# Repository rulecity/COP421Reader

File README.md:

# COP421Reader
This is a hardware reader for the COP421 Microcontroller.

I designed it very quickly just to read the COP421 microcontroller used by the RDI Halcyon (since I have/had one temporarily on loan).  It turns out it's identical to the Thayer's Quest arcade COP421 program, but it's nice to know for sure.

I relied heavily on the information at this page to contruct my reader: http://john.ccac.rwth-aachen.de:8000/patrick/COPSreader.htm

## Building
### KiCad files
I started with an EAGLE project that I made for Star Rider for this PCB, so you will see references to Star Rider in the Kicad project.  I imported some EAGLE symbols and used some native Kicad symbols so you'll see a hybrid of both.  (like I said, this was a quick n' dirty project since I intended it to only be used once).  I used KiCad v6 for this project.

### AVR files
Source code for the ATMega644p microcontroller, as well as a Makefile and a script to install via AVR Dragon / AVRDude.
The AVR reads from the COP421 and outputs the resulting data to USB serial port.

### Desktop
Source code to build a simple desktop (Windows/Linux/Mac) application to read the data from the AVR (via USB serial port) and save to a file.

### Bill of Materials
CSV file showing which parts I used on the PCB.

## Running
- Put COP421 into ZIF socket in custom PCB.
- Power on custom PCB with 5V wall wart.
- Plug in USB cable from desktop device (Windows/Linux/Mac) into custom PCB.  The USB serial device should be registered automatically.
- Run the desktop command line application.  You should see a "Listening" prompt.
- Hit the RESET button on the custom PCB.
- After a few seconds, the desktop app should report CRC success or fail.  On success, it will report the file path that it has written the dumped binary to.  You may repeat this (by repeatedly pressing RESET) to confirm that you've got a consistent read.

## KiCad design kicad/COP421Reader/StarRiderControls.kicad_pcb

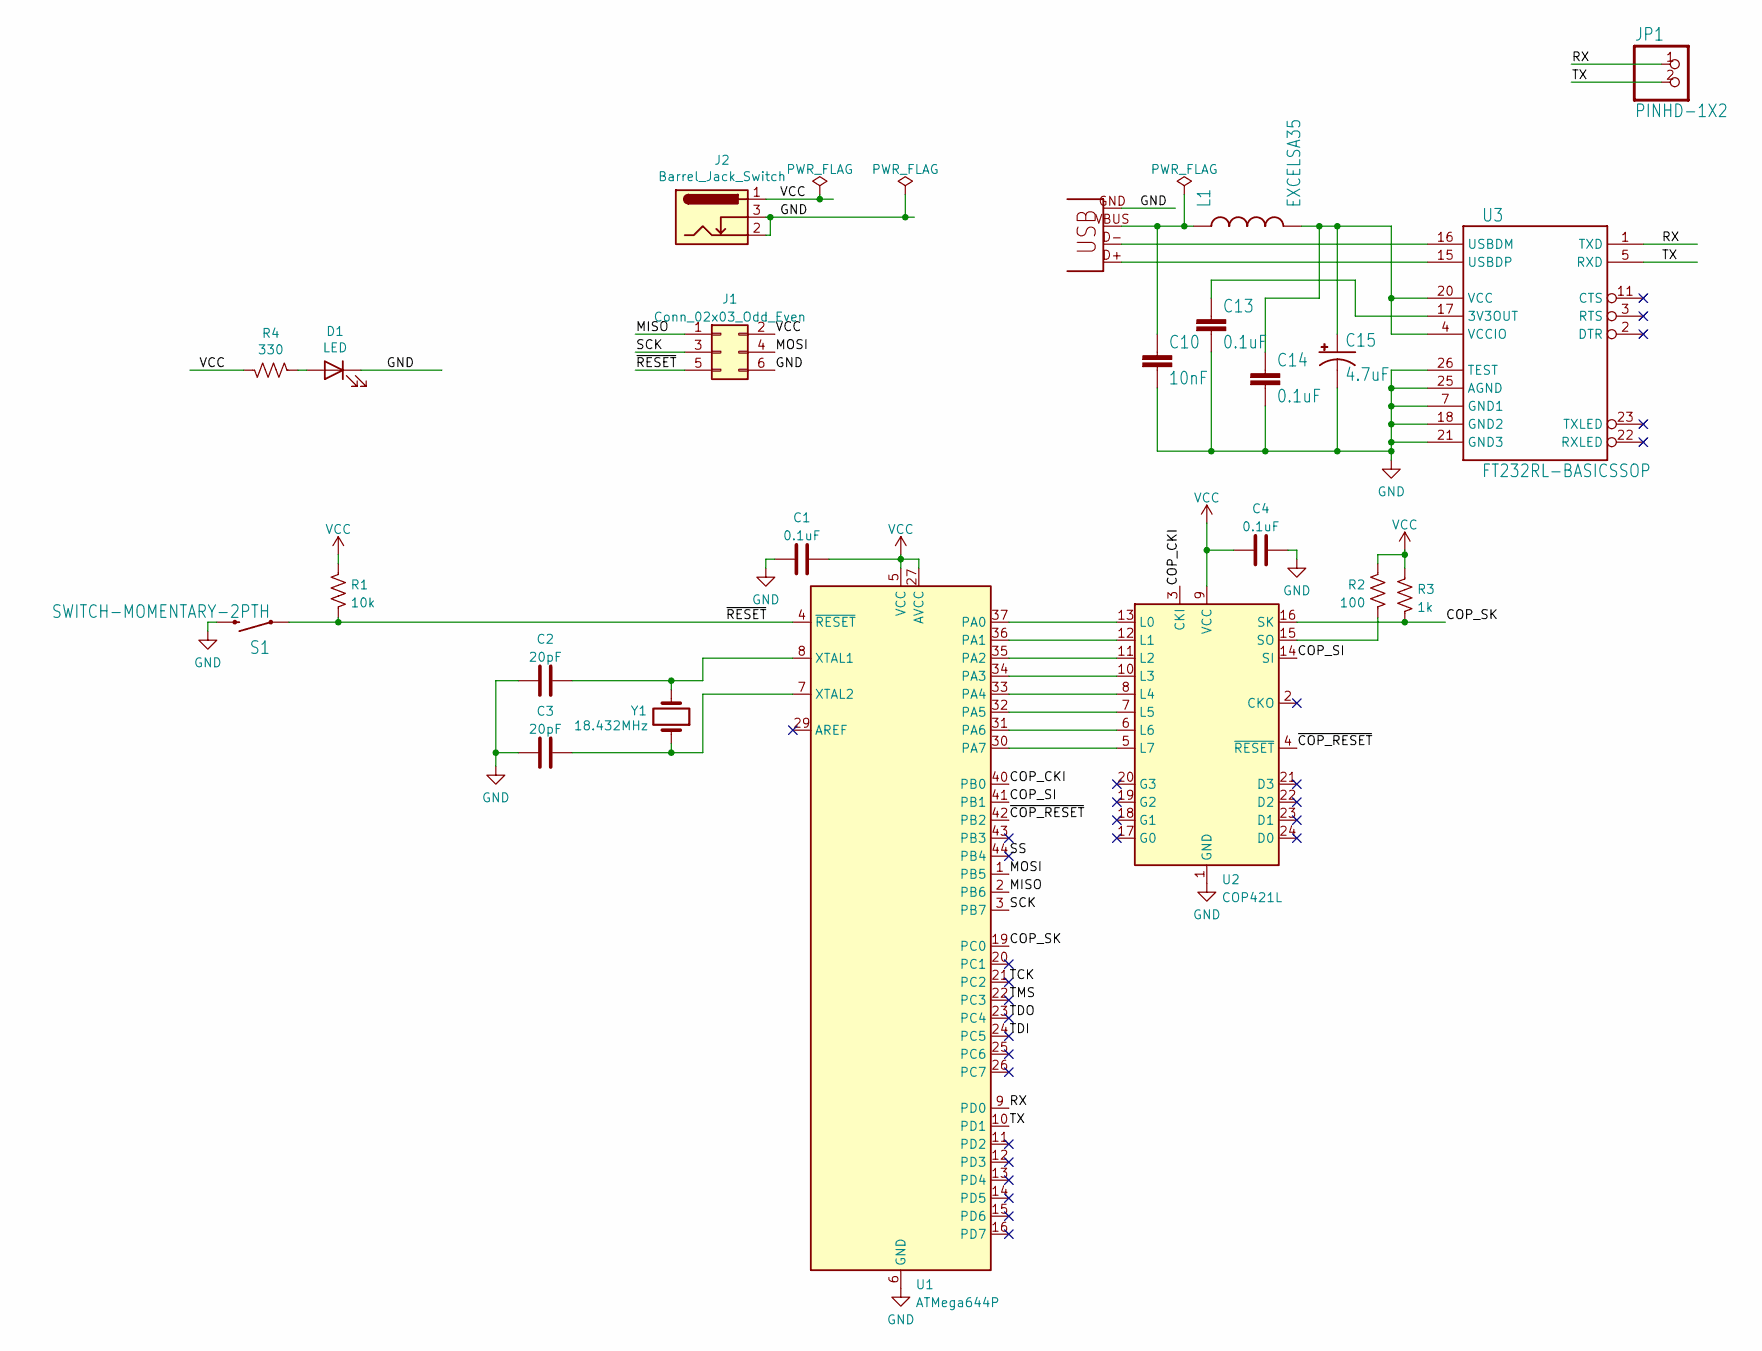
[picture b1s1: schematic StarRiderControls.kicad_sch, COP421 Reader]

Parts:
C1, C4, C13, C14: 0.1uF; C_1206_3216Metric_Pad1.33x1.80mm_HandSolder
C2, C3: 20pF; C_1206_3216Metric_Pad1.33x1.80mm_HandSolder
C10: 10nF; C_1206_3216Metric_Pad1.33x1.80mm_HandSolder
C15: 4.7uF; EIA3216
D1: LED; LED_1206_3216Metric_Pad1.42x1.75mm_HandSolder
J1: Conn_02x03_Odd_Even; PinHeader_2x03_P2.54mm_Vertical
J2: Barrel_Jack_Switch; BarrelJack_Horizontal
JP1: PINHD-1X2; 1X02
L1: EXCELSA35
R1: 10k; R_1206_3216Metric_Pad1.30x1.75mm_HandSolder
R2: 100; R_1206_3216Metric_Pad1.30x1.75mm_HandSolder
R3: 1k; R_1206_3216Metric_Pad1.30x1.75mm_HandSolder
R4: 330; R_1206_3216Metric_Pad1.30x1.75mm_HandSolder
S1: SWITCH-MOMENTARY-2PTH; TACTILE-PTH
U1: ATMega644P; TQFP-44_10x10mm_P0.8mm
U2: COP421L; DIP-24_W15.24mm_Socket
U3: FT232RL-BASICSSOP; SSOP-28_5.3x10.2mm_P0.65mm
X5: USBPTH; USB-B-PTH
Y1: 18.432MHz; CRYSTAL-CSM-3X

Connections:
/COP_CKI: U1.40 (PB0), U2.3 (CKI)
/COP_SI: U1.41 (PB1), U2.14 (SI)
/COP_SK: R3.2, U1.19 (PC0), U2.16 (SK)
/MISO: J1.1, U1.2 (PB6)
/MOSI: J1.4, U1.1 (PB5)
/RX: JP1.1, U1.9 (PD0), U3.1 (TXD)
/SCK: J1.3, U1.3 (PB7)
/SS: U1.44 (PB4)
/TCK: U1.21 (PC2)
/TDI: U1.24 (PC5)
/TDO: U1.23 (PC4)
/TMS: U1.22 (PC3)
/TX: JP1.2, U1.10 (PD1), U3.5 (RXD)
/~COP_RESET: U1.42 (PB2), U2.4 (~RESET)
/~RESET: J1.5, R1.2, S1.1, U1.4 (~RESET)
GND: C1.2, C2.2, C3.2, C4.1, C10.2, C13.2, C14.2, C15.C (-), D1.1 (K), J1.6, J2.2, J2.3, S1.3 (2), U1.6 (GND), U1.18 (GND), U1.28 (GND), U1.39 (GND), U2.1 (GND), U3.7 (GND1), U3.18 (GND2), U3.21 (GND3), U3.25 (AGND), U3.26 (TEST), X5.GND
unnamed: C2.1, U1.8 (XTAL1), Y1.2
unnamed: C3.1, U1.7 (XTAL2), Y1.1
unnamed: C10.1, L1.P1 (1), X5.VBUS
unnamed: C13.1, U3.17 (3V3OUT)
unnamed: C14.1, C15.A (+), L1.P2 (2), U3.4 (VCCIO), U3.20 (VCC)
unnamed: D1.2 (A), R4.2
unnamed: R2.1, U2.15 (SO)
unnamed: U1.30 (PA7), U2.5 (L7)
unnamed: U1.31 (PA6), U2.6 (L6)
unnamed: U1.32 (PA5), U2.7 (L5)
unnamed: U1.33 (PA4), U2.8 (L4)
unnamed: U1.34 (PA3), U2.10 (L3)
unnamed: U1.35 (PA2), U2.11 (L2)
unnamed: U1.36 (PA1), U2.12 (L1)
unnamed: U1.37 (PA0), U2.13 (L0)
unnamed: U3.15 (USBDP), X5.D+
unnamed: U3.16 (USBDM), X5.D-
VCC: C1.1, C4.2, J1.2, J2.1, R1.1, R2.2, R3.1, R4.1, U1.5 (VCC), U1.17 (VCC), U1.27 (AVCC), U1.38 (VCC), U2.9 (VCC)

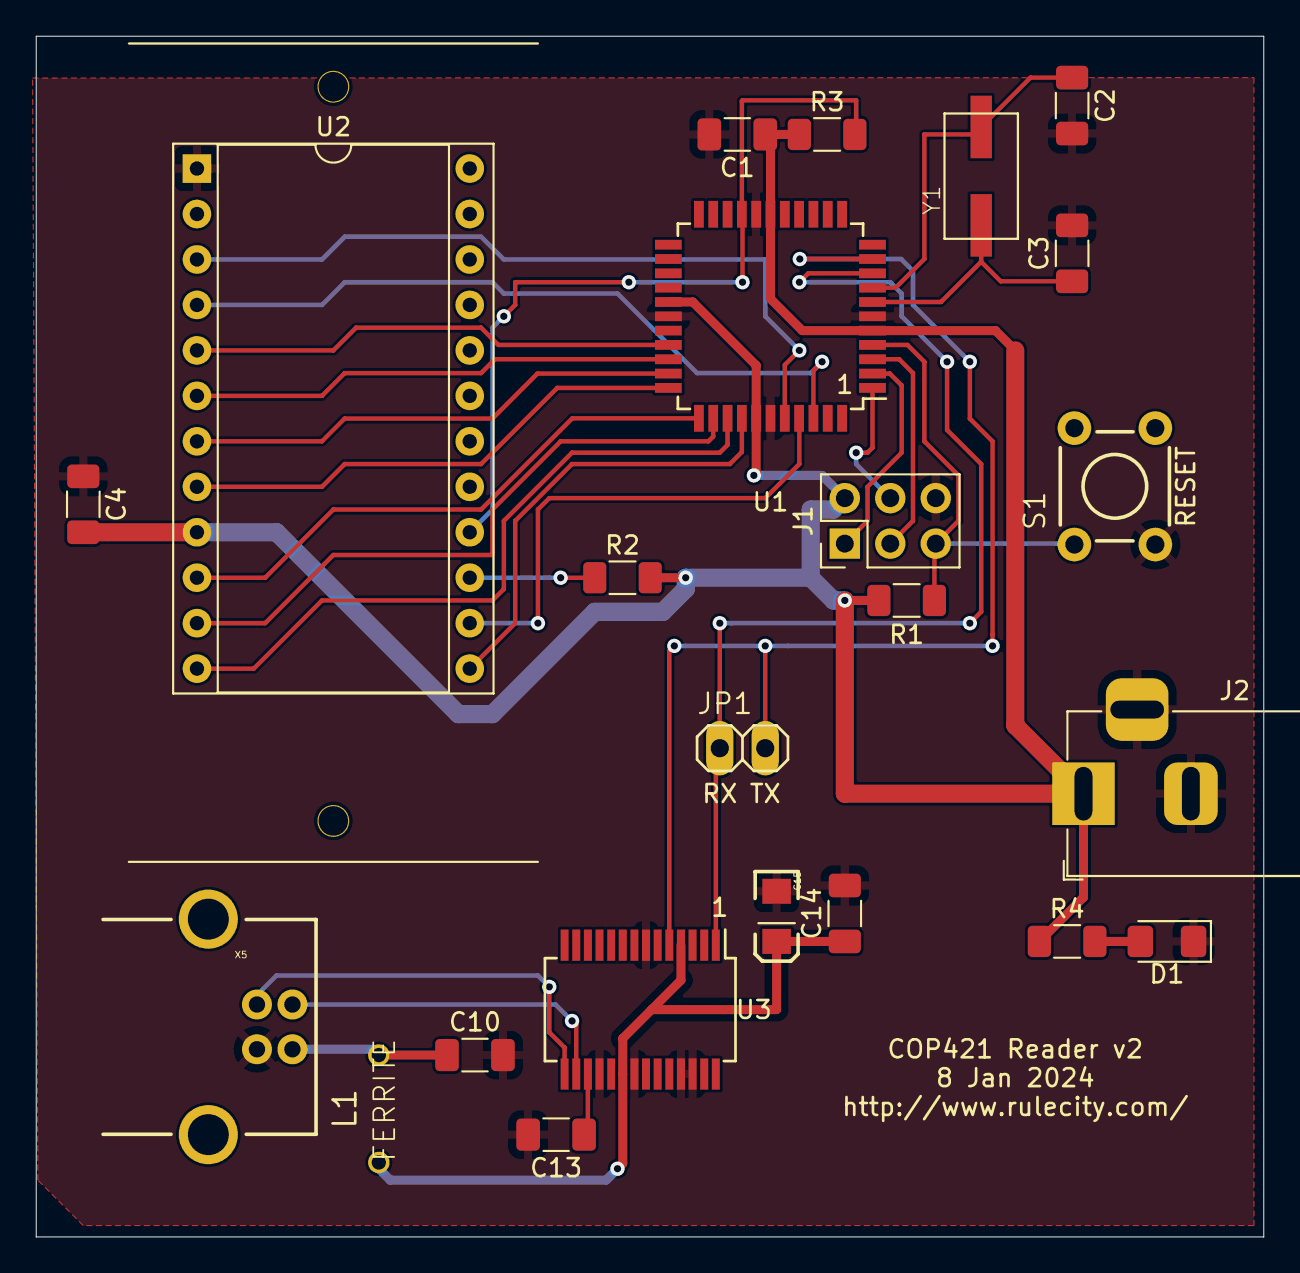
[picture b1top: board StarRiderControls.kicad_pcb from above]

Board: 2 copper layers, 68.6 x 67.1 mm, 23 parts (0 on the bottom side), 29 nets.

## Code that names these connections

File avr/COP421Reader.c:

// COP421 Reader
// By Matt Ownby
// Jan 2024

// Very quick and dirty.  This was to read a single microcontroller so I just put enough effort into it to get it working.
// Thanks to http://john.ccac.rwth-aachen.de:8000/patrick/COPSreader.htm for doing most of the work and the excellent documentation.
// Final design's CKI runs at about 250 kHz and it still works.  I could've written this in assembly language and increased CKI speed but it wasn't worth it.

// This program dumps 1k bytes + 2 CRC bytes at 115200 bps over AVR's USART serial lines.

#include <stdio.h>
#include <avr/io.h> 
#include <avr/interrupt.h>
#include "serial.h"
#include "crc.h"

/////////////////////////////////////////////////////

#define WAIT_FALL()		while ((PINC & (1 << PC0)) != 0) { fastClockThink(); }
#define WAIT_RISE()		while ((PINC & (1 << PC0)) == 0) { fastClockThink(); }

//////////////////////////////////////

// to manage output clock that we generate
uint8_t g_u8COP421CkiIsHigh = 0;

// to hold buffer that we read from COP
uint16_t g_u16BufferCount = 0;
uint8_t *g_pBufferPtr = 0;
uint8_t g_arrCOPBuffer[1024];

inline void fastClockThink()
{
	// make fast clock tick
	if (TIFR0 & (1 << OCF0A))
	{
		g_u8COP421CkiIsHigh ^= 1;

		PORTB &= ~(1 << PB0);
		PORTB |= (g_u8COP421CkiIsHigh << PB0);

		TIFR0 |= (1 << OCF0A);	// clear CTC flag
	}
}

inline void insertByte(uint8_t u8Byte)
{
	PORTA = u8Byte;

	// wait for SK's next falling edge
	WAIT_FALL();

	// wait for SK's next rising edge
	WAIT_RISE();
}

int main (void) 
{
	uint8_t u8CyclesElapsed64k = 0;

	uint8_t u8Tmp = 0;

	serial_init();

	// Setup 16-bit timer
	TCCR1A = (1 << WGM11);	// enable CTC
	TCCR1B = (1 << CS10) | (1 << CS11);	// /64 prescaling
	OCR1B = 0xFFF0;	// ~64k worth of cycles

	// Setup 8-bit timer
	TCCR0A = (1 << WGM01);	// enable CTC
	TCCR0B = (1 << CS00);	// no-prescaling
	OCR0A = 36;	// CTC every 36 cycles (this makes outgoing clock run at about 250 kHz)

	// go into output mode for CKI, SI, and RESET
	DDRB = (1 << PB0) | (1 << PB1) | (1 << PB2);

	// set CKI, SI and RESET low
	PORTB = (0 << PB0) | (0 << PB1) | (0 << PB2);

	// go into input mode for SK
	DDRC = (0 << PC0);

	// start in input mode for L0-L7 to be safe
	DDRA = 0;

	// start tracking 16-bit timer so we know how many cycles have elapsed
	TCNT1 = 0;

	// enable interrupts now that we are initialized
	sei();

	///////////////////

	// POWER ON STAGE

	// played around with this value until I got a ~130ms setup time
	while (u8CyclesElapsed64k < 37)
	{
		fastClockThink();

		// if 64k cycles have elapsed
		if (TIFR1 & (1 << OCF1A))
		{
			TIFR1 |= (1 << OCF1A);	// clear CTC flag
			u8CyclesElapsed64k++;
		}
	}

	// wait for SK's next rising edge
	WAIT_RISE();

	// raise SI and RESET'
	PORTB |= (1 << PB1)|(1 << PB2);

	// wait for SK's next falling edge
	WAIT_FALL();

	// wait for SK's next rising edge
	WAIT_RISE();

	// at this point, the COP is ready for us to insert instructions

	DDRA = 0xFF;	// go into output mode

	// This sends the initial program needed to put the COP in "ROM dump" mode
	insertByte(0);	// CLRA
	insertByte(0x63);
	insertByte(0xFC);
	insertByte(0xBF);
	insertByte(0x44);
	insertByte(0x33);
	insertByte(0x64);

	// SPECIAL BEHAVIOR LAST INSERTED BYTE

	PORTA = 0x44;	// NOP

	// wait for SK's next falling edge
	WAIT_FALL();

	// NEED TO LOWER SI IN MIDDLE OF SK

	u8Tmp = 0;
	
	// SK period is 16 of our fast clocks, so we go at 11 at recommendation of blog post
	while (u8Tmp < 11)
	{
		// make fast clock tick
		if (TIFR0 & (1 << OCF0A))
		{
			g_u8COP421CkiIsHigh ^= 1;

			PORTB &= ~(1 << PB0);
			PORTB |= (g_u8COP421CkiIsHigh << PB0);

			TIFR0 |= (1 << OCF0A);	// clear CTC flag

			if (g_u8COP421CkiIsHigh)
			{
				u8Tmp++;
			}
		}
	}

	// PREPARE TO READ BYTES

	PORTB &= ~(1 << PB1);	// LOWER SI
	DDRA = 0;	// INPUT MODE FOR DATA BUS

	WAIT_RISE();

	// At this point, the first byte of the program will be put on the data bus as soon as SK falls

	g_pBufferPtr = g_arrCOPBuffer;
	g_u16BufferCount = 0;

	// read in the 1k program
	while (g_u16BufferCount < sizeof(g_arrCOPBuffer))
	{
		WAIT_FALL();
		
		// byte of program will be put on data bus shortly after this point; we'll wait until rising edge to guarantee that it's there

		WAIT_RISE();

		*g_pBufferPtr = PINA;

		g_pBufferPtr++;
		g_u16BufferCount++;
	}

	// go back into init/reset state for COP so it's not doing anything with the bus
	PORTB = (0 << PB0) | (0 << PB1) | (0 << PB2);

	// DUMP BUFFER OUT TO SERIAL PORT
	
	g_pBufferPtr = g_arrCOPBuffer;
	g_u16BufferCount = 0;
	crc_ccitt_init();

	while (g_u16BufferCount < sizeof(g_arrCOPBuffer))
	{
		uint8_t u8 = *g_pBufferPtr;
		tx_to_buf(u8);
		crc_ccitt_update(u8);
		g_pBufferPtr++;
		g_u16BufferCount++;
	}

	// send CRC value (lil endian)
	tx_to_buf(crc_ccitt_crc() & 0xFF);
	tx_to_buf(crc_ccitt_crc() >> 8);

	// program done!
	for (;;)
	{
	}
	
}

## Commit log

2024-01-15 added desktop app
2024-01-16 added bill of materials
2024-01-16 added example picture
2024-01-16 Update README.md
    added usage section
2024-01-16 updated instructions, removed unnecessary stuff from makefile
